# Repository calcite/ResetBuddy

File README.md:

RESET BUDDY
==============
This device provides 9 relay outputs with a current rating up to 5A each. It can be fully powered and controlled by standard USB bus. Green LED mounted right next to corresponding relay indicates its state.

connector: 	USB mini type B
		Pluggable screw terminal AWG 16 - 26 

Board designed with KiCad 4.0.2

Box designed with freecad, based on HAMMOND 1455L1202

Controlling MCP2210:

Installation of lib_usb which in needed for running MCP2210
```
$apt-get update
$apt-get upgrade
$apt-get install python3-dev
$apt-get install cython3
$apt-get install libusb-1.0.0 libusb-1.0.0-dev libudev-dev
$pip3 install hidapi
```

Testing can be made with microchip utility: http://ww1.microchip.com/downloads/en/DeviceDoc/MCP2210Utility_v1.2.2.zip
Full control can be reached with utility attached to this project (RB utility).

RB utility control:
run python script with paramethers. Syntax is:
python RB_utility.py <operation><pin><state>[time]	parameter time is not obligatory

supported operations: 	
- set = s		– sets or clears pin (puts the pin into state 0 or 1)
- get = g	– reads state of pin
- reset = r	– sets pin for time (in seconds), then clears it
- rev_reset = rev – opposite of reset
- clearall = c	- clears all pins
- test = t	- visual test
- crazy! 		- even better test

For some operations there is no need for all other parameters but you always have to put them in (poor programming skills). 

allowed pin inputs: 1,2,3,4,5,6,7,8,9,all,a,x	(a = all, x for operations without pin input)

allowed state iputs: 0,1,x			(x for operations without state input)

time parameter only for reset operation. You must put –t ahead of the parameter itself

examples:
```
python RB_utility.py set 1 1	//sets pin 1 into logic 1
python RB_utility.py r 9 x –t 1	//sets pin 9 for 1 second, then clears it 
python RB_utility.py crazy! x x 	//just try it ;) 
```

love is all around us

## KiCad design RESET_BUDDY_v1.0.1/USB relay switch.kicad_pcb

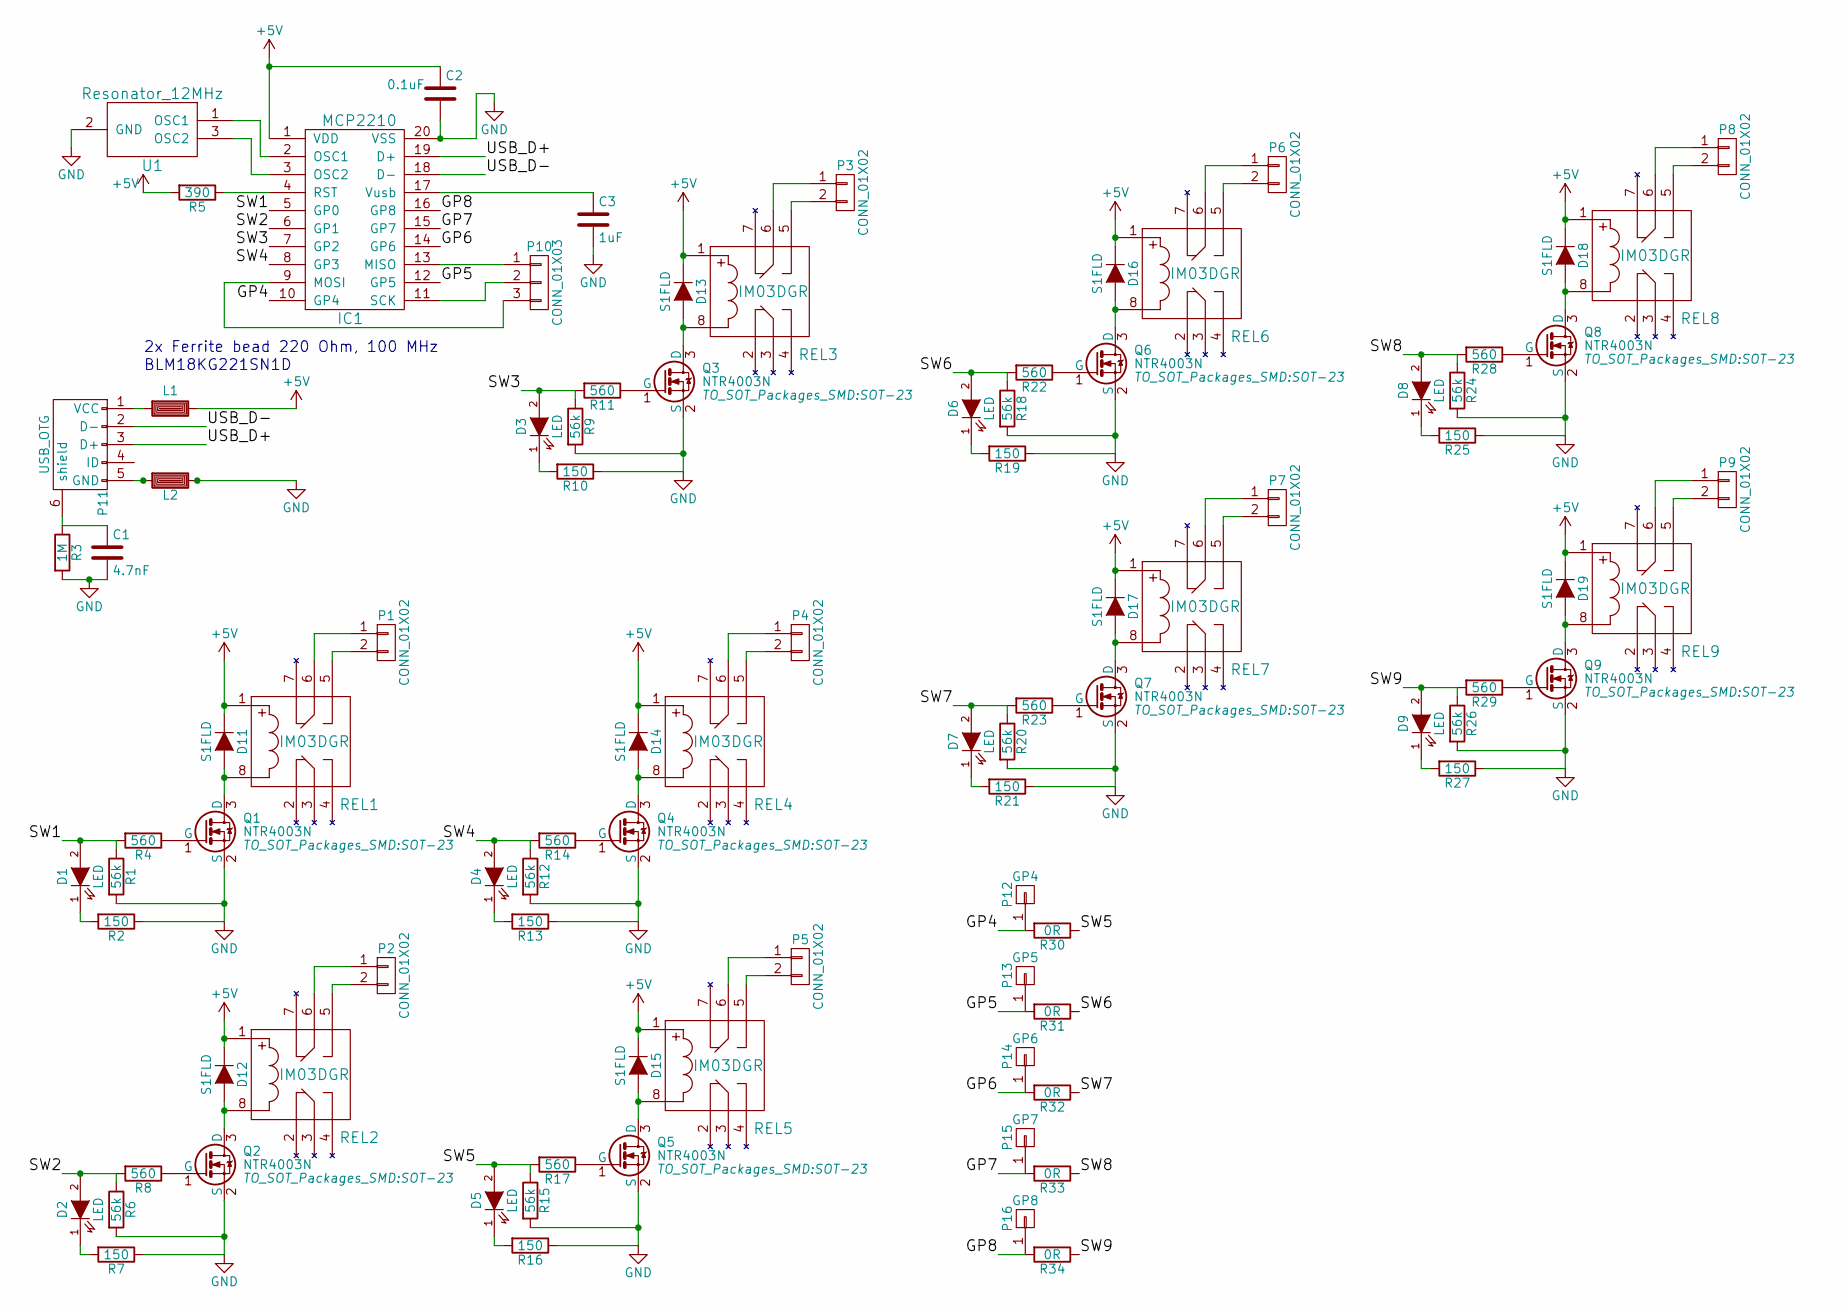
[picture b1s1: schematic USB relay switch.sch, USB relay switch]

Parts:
C1: 4.7nF; C_0805_HandSoldering
C2: 0.1uF; C_0805_HandSoldering
C3: 1uF; C_0805_HandSoldering
D1, D2, D3, D4, D5, D6, D7, D8, D9: LED; LED-3MM
D11, D12, D13, D14, D15, D16, D17, D18, D19: S1FLD; DO-219AB_SMF
IC1: MCP2210; SOIC-20_7.5x12.8mm_Pitch1.27mm
L1, L2: FER; R_0603_HandSoldering
P1, P2, P3, P4, P5, P6, P7, P8, P9: CONN_01X02; CTB932HD2
P10: CONN_01X03; Pin_Header_Straight_1x03
P11: USB_OTG; USB_Mini-B
P12: GP4; Pin_Header_Straight_1x01
P13: GP5; Pin_Header_Straight_1x01
P14: GP6; Pin_Header_Straight_1x01
P15: GP7; Pin_Header_Straight_1x01
P16: GP8; Pin_Header_Straight_1x01
Q1, Q2, Q3, Q4, Q5, Q6, Q7, Q8, Q9: NTR4003N; SOT-23
R1, R6, R9, R12, R15, R18, R20, R24, R26: 56k; R_0805_HandSoldering
R2, R7, R10, R13, R16, R19, R21, R25, R27: 150; R_0805_HandSoldering
R3: 1M; R_0805_HandSoldering
R4, R8, R11, R14, R17, R22, R23, R28, R29: 560; R_0805_HandSoldering
R5: 390; R_0805_HandSoldering
R30, R31, R32, R33, R34: 0R; R_0805_HandSoldering
REL1, REL2, REL3, REL4, REL5, REL6, REL7, REL8, REL9: IM03DGR
U1: Resonator_12MHz; rezonator_murrata

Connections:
+5V: C2.1, D11.1 (K), D12.1 (K), D13.1 (K), D14.1 (K), D15.1 (K), D16.1 (K), D17.1 (K), D18.1 (K), D19.1 (K), IC1.1 (VDD), L1.1, R5.2, REL1.1, REL2.1, REL3.1, REL4.1, REL5.1, REL6.1, REL7.1, REL8.1, REL9.1
/GP4: IC1.10 (GP4), P12.1, R30.2
/GP5: IC1.12 (GP5), P13.1, R31.2
/GP6: IC1.14 (GP6), P14.1, R32.2
/GP7: IC1.15 (GP7), P15.1, R33.2
/GP8: IC1.16 (GP8), P16.1, R34.2
/SW1: D1.2 (A), IC1.5 (GP0), R1.1, R4.2
/SW2: D2.2 (A), IC1.6 (GP1), R6.1, R8.2
/SW3: D3.2 (A), IC1.7 (GP2), R9.1, R11.2
/SW4: D4.2 (A), IC1.8 (GP3), R12.1, R14.2
/SW5: D5.2 (A), R15.1, R17.2, R30.1
/SW6: D6.2 (A), R18.1, R22.2, R31.1
/SW7: D7.2 (A), R20.1, R23.2, R32.1
/SW8: D8.2 (A), R24.1, R28.2, R33.1
/SW9: D9.2 (A), R26.1, R29.2, R34.1
/USB_D+: IC1.19 (D+), P11.3 (D+)
/USB_D-: IC1.18 (D-), P11.2 (D-)
GND: C1.2, C2.2, C3.2, IC1.20 (VSS), L2.1, Q1.2 (S), Q2.2 (S), Q3.2 (S), Q4.2 (S), Q5.2 (S), Q6.2 (S), Q7.2 (S), Q8.2 (S), Q9.2 (S), R1.2, R2.1, R3.2, R6.2, R7.1, R9.2, R10.1, R12.2, R13.1, R15.2, R16.1, R18.2, R19.1, R20.2, R21.1, R24.2, R25.1, R26.2, R27.1, U1.2 (GND)
unnamed: C1.1, P11.6 (shield), R3.1
unnamed: C3.1, IC1.17 (Vusb)
unnamed: D1.1 (K), R2.2
unnamed: D2.1 (K), R7.2
unnamed: D3.1 (K), R10.2
unnamed: D4.1 (K), R13.2
unnamed: D5.1 (K), R16.2
unnamed: D6.1 (K), R19.2
unnamed: D7.1 (K), R21.2
unnamed: D8.1 (K), R25.2
unnamed: D9.1 (K), R27.2
unnamed: D11.2 (A), Q1.3 (D), REL1.8
unnamed: D12.2 (A), Q2.3 (D), REL2.8
unnamed: D13.2 (A), Q3.3 (D), REL3.8
unnamed: D14.2 (A), Q4.3 (D), REL4.8
unnamed: D15.2 (A), Q5.3 (D), REL5.8
unnamed: D16.2 (A), Q6.3 (D), REL6.8
unnamed: D17.2 (A), Q7.3 (D), REL7.8
unnamed: D18.2 (A), Q8.3 (D), REL8.8
unnamed: D19.2 (A), Q9.3 (D), REL9.8
unnamed: IC1.2 (OSC1), U1.1 (OSC1)
unnamed: IC1.3 (OSC2), U1.3 (OSC2)
unnamed: IC1.4 (RST), R5.1
unnamed: IC1.9 (MOSI), P10.3
unnamed: IC1.11 (SCK), P10.2
unnamed: IC1.13 (MISO), P10.1
unnamed: L1.2, P11.1 (VCC)
unnamed: L2.2, P11.5 (GND)
unnamed: P1.1, REL1.6
unnamed: P1.2, REL1.5
unnamed: P2.1, REL2.6
unnamed: P2.2, REL2.5
unnamed: P3.1, REL3.6
unnamed: P3.2, REL3.5
unnamed: P4.1, REL4.6
unnamed: P4.2, REL4.5
unnamed: P5.1, REL5.6
unnamed: P5.2, REL5.5
unnamed: P6.1, REL6.6
unnamed: P6.2, REL6.5
unnamed: P7.1, REL7.6
unnamed: P7.2, REL7.5
unnamed: P8.1, REL8.6
unnamed: P8.2, REL8.5
unnamed: P9.1, REL9.6
unnamed: P9.2, REL9.5
unnamed: Q1.1 (G), R4.1
unnamed: Q2.1 (G), R8.1
unnamed: Q3.1 (G), R11.1
unnamed: Q4.1 (G), R14.1
unnamed: Q5.1 (G), R17.1
unnamed: Q6.1 (G), R22.1
unnamed: Q7.1 (G), R23.1
unnamed: Q8.1 (G), R28.1
unnamed: Q9.1 (G), R29.1

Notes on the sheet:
2x Ferrite bead 220 Ohm, 100 MHz
BLM18KG221SN1D

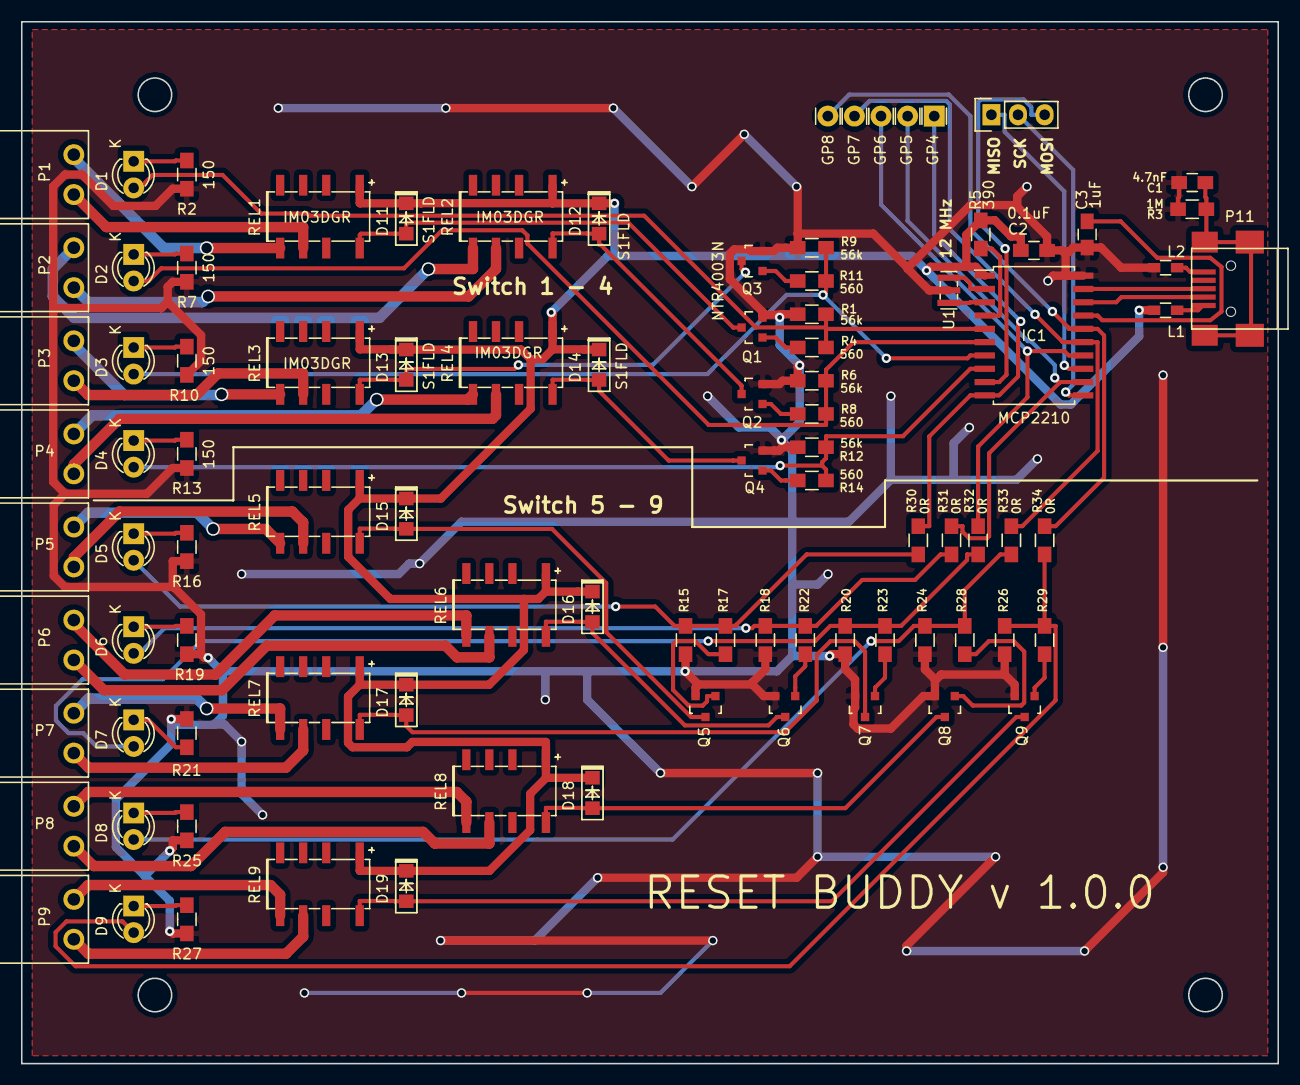
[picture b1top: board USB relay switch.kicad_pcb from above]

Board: 2 copper layers, 120.0 x 99.5 mm, 93 parts (0 on the bottom side), 73 nets.

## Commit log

2017-01-16 first commit - create repository
2017-01-16 RESET BUDDY reached internet!
2017-01-16 deleting pictures
2017-01-16 Until now it was just a game. Now we have a serious project here.
2017-01-16 folder repair
2017-01-16 new readmei
2017-01-16 readme is the most precious file and must be modified multiple times
2017-01-16 readme update
2017-01-17 deleting old version
